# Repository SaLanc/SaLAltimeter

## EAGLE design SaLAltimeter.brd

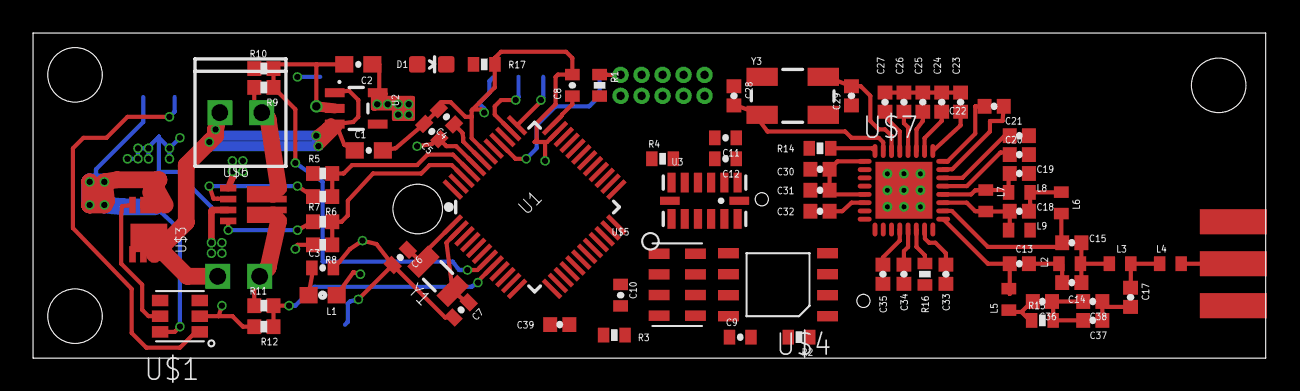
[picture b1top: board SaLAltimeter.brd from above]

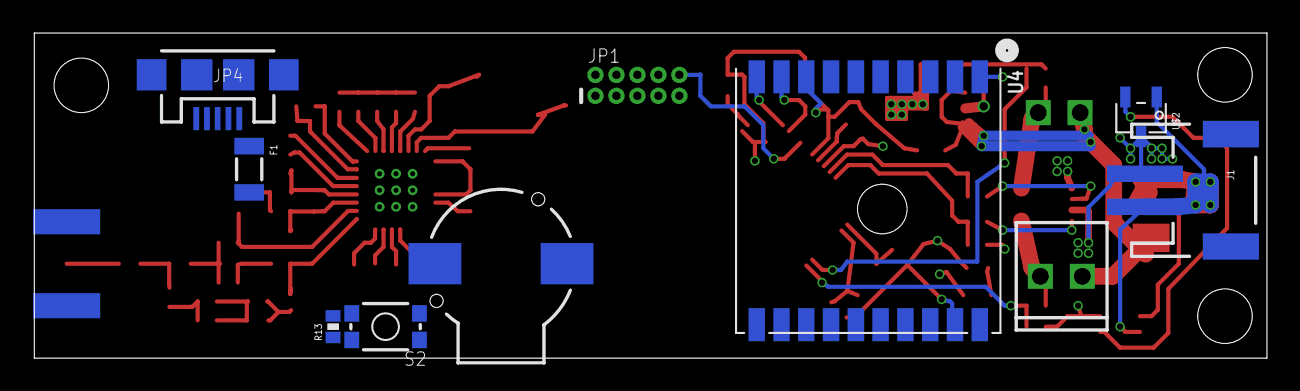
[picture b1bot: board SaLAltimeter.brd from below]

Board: 4 copper layers, 74.6 x 19.7 mm, 91 parts (10 on the bottom side), 56 nets.

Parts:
C1: 1.0uF; 0603-CAP
C2: 2.2uF; 0603-CAP
C3, C4, C5, C9, C10, C11, C39: 0.1uF; 0402-CAP
C6, C7, C28, C29: 15pF; 0402-CAP
C8: 0402-CAP
C12: 10uF; 0402-CAP
C13: 39pF; 0402-CAP
C14: 2.2pF; 0402-CAP
C15, C18, C19: 5.1pF; 0402-CAP
C17: 6.2pF; 0402-CAP
C20, C37: 10nF; 0402-CAP
C21, C23, C24, C25, C26, C27, C30, C31, C33, C34, C35: 47nF; 0402-CAP
C22: 1.8nF; 0402-CAP
C32: 220nF; 0402-CAP
C36: 56pF; 0402-CAP
C38: 100pF; 0402-CAP
D1: RED; LED-0603
F1: PTCSMD; PTC-1206
FRAME1: FRAME-LEDGER; CREATIVE_COMMONS
J1: JST-2-SMD
J$1: SMA_EDGE; SMA-EDGE
JP1: CORTEX_DEBUGPTH; 2X5-PTH-1.27MM
JP2, JP3: 1X02_2.54_SCREWTERM
JP4: USB-MICROB
L1: FB - 30Ohm; 0603
L2, L6: 15nH; C0402
L3: 43nH; C0402
L4: 22nH; C0402
L5, L7: 56nH; C0402
L8, L9: 27nH; C0402
R1, R2, R3, R4, R13, R15: 0402-RES
R5, R6, R7, R8, R9, R10, R11, R12: 10kohm; 0402-RES
R14: 0ohm; 0402-RES
R16: 56KOhm; 0402-RES
R17: 301ohm\; 0402-RES
S2: SWITCH-MOMENTARY-2SMD-4.6X2.8MM; TACTILE_SWITCH_SMD_4.6X2.8MM
SG1: BUZZERSMD2; BUZZER-CCV
STANDOFF1, STANDOFF2, STANDOFF3: STAND-OFF
U1: ATSAMD21G-A; TQFP-48
U2: V_REG_LDOSMD; SOT23-5
U3: ADXL345; LGA14
U4: FGPMMOPA6H
U$1: MAX16054
U$2: SS345PT
U$3: SI7615ADN
U$4: AT25SF081
U$5: SIMPLE-MS5607; MS5607
U$6: SI7232DN
U$7: CC1120
Y1: CRYSTAL-SMD-3.2X1.5MM
Y3: 32MHz; CRYSTAL-SMD-5X3

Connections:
3.3V: C2.1, C5.1, C8.1, C9.1, C10.1, C11.1, C12.1, C21.1, C25.2, C26.2, C30.2, C31.2, C33.2, C34.2, C35.2, C36.1, C37.2, C38.2, C39.2, JP1.1, L1.1, R1.2, R2.2, R3.2, R4.2, R15.2, S2.3, S2.4, U1.17, U1.36, U1.44, U2.5, U3.1, U3.6, U4.P$1, U$4.!HOLD, U$4.!WP, U$4.VCC, U$5.1, U$7.1, U$7.5, U$7.12, U$7.13, U$7.15, U$7.22, U$7.27, U$7.28
!RESET: JP1.10, R1.1, U1.40
BUZZER: SG1.-, U1.27
CS_ACCEL: R4.1, U1.24, U3.7
CS_BARO: R3.1, U1.22, U$5.4, U$5.5
CS_MEM: R2.1, U1.23, U$4.!CS
CS_TX: U1.28, U$7.11
FET_A: JP2.P1, R9.2, U$6.7, U$6.8
FET_B: JP3.P1, R11.1, U$6.5, U$6.6
FIRE_A: R5.2, R6.1, U1.45
FIRE_B: R7.2, R8.1, U1.46
GATE: U$1.OUT, U$3.G
GND: C1.2, C2.2, C3.2, C4.2, C5.2, C6.2, C7.2, C8.2, C9.2, C10.2, C11.2, C12.2, C17.2, C19.2, C20.2, C21.2, C23.1, C24.1, C25.1, C26.1, C27.1, C28.1, C29.1, C30.1, C31.1, C32.1, C33.1, C34.1, C35.1, C37.1, C38.1, C39.1, J1.1, J$1.GND@0, J$1.GND@1, J$1.GND@2, J$1.GND@3, JP1.3, JP1.5, JP4.GND, JP4.MT1, JP4.MT2, L9.2, R5.1, R8.2, R10.1, R12.2, R13.1, R14.2, R16.2, R17.1, SG1.+, U1.5, U1.18, U1.35, U1.42, U2.2, U3.2, U3.4, U3.5, U4.P$3, U4.P$8, U4.P$12, U4.P$19, U$1.GND, U$2.GND, U$4.GND, U$5.2, U$5.3, U$6.1, U$6.3
GPS_RX: U1.38, U4.P$9
GPS_TX: U1.37, U4.P$10
LVD_IN: C1.1, JP2.P2, JP3.P2, U2.1, U2.3, U$3.D1, U$3.D2, U$3.D3, U$3.D4
unnamed: R6.2, U$6.2
unnamed: U$1.IN, U$2.OUT
unnamed: C6.1, U1.1, Y1.P$2
unnamed: C7.1, U1.2, Y1.P$1
unnamed: C3.1, L1.2
unnamed: C4.1, U1.43
unnamed: R7.1, U$6.4
unnamed: C13.1, L5.2, U$7.17
unnamed: C13.2, C14.1, L2.1
unnamed: C14.2, C15.1, L2.2, L3.1
unnamed: C17.1, L3.2, L4.1
unnamed: J$1.SIG, L4.2
unnamed: F1.1, JP4.VBUS
unnamed: C23.2, U$7.25
unnamed: C15.2, L6.2, U$7.18
unnamed: C18.1, L7.2, L9.1, U$7.19
unnamed: C18.2, L6.1, L8.2
unnamed: C19.1, L7.1, L8.1, U$7.20
unnamed: C22.1, U$7.24
unnamed: C22.2, U$7.23
unnamed: C20.1, U$7.21
unnamed: C24.2, U$7.26
unnamed: R16.1, U$7.14
unnamed: R14.1, U$7.32
unnamed: C27.2, U$7.29
unnamed: C29.2, U$7.30, Y3.3
unnamed: C28.2, U$7.31, Y3.1
unnamed: D1.C, R17.2
unnamed: D1.A, U4.P$5
unnamed: C32.2, U$7.6
unnamed: C36.2, L5.1, R15.1
PROG: R13.2, S2.1, S2.2, U1.29
RAW: J1.2, U$1.VCC, U$2.VCC, U$3.S1, U$3.S2, U$3.S3
SENSE_A: R9.1, R10.2, U1.7
SENSE_B: R11.2, R12.1, U1.8
SPI_MISO: U1.21, U1.25, U3.12, U$4.SO, U$5.6, U$7.9
SPI_MOSI: U1.19, U1.26, U3.13, U$4.SI, U$5.7, U$7.7
SPI_SCK: U1.20, U3.14, U$4.SCK, U$5.8, U$7.8
USB_D+: JP4.D+, U1.34
USB_D-: JP4.D-, U1.33

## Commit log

2015-12-27 :tada: Added .gitattributes & .gitignore files
2015-12-27 setting up board
2015-12-27 added transmiter
2015-12-27 fixed gps
2015-12-28 aligned tx parts
2015-12-28 starting 4 layer routing
2015-12-28 lots of work on the layout
2015-12-28 squished it all inside
2015-12-29 starting wiring
2015-12-29 more wiring
2015-12-30 finshed wiring
2015-12-30 mk1 finished!
2016-01-18 parts lists added

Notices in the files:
parts and their libraries:
SparkFun-Aesthetics: Licensing: Creative Commons ShareAlike 4.0 International - https://creativecommons.org/licenses/by-sa/4.0
SparkFun-Aesthetics: Released under the Creative Commons Attribution Share-Alike 4.0 License
SparkFun-Aesthetics: https://creativecommons.org/licenses/by-sa/4.0
